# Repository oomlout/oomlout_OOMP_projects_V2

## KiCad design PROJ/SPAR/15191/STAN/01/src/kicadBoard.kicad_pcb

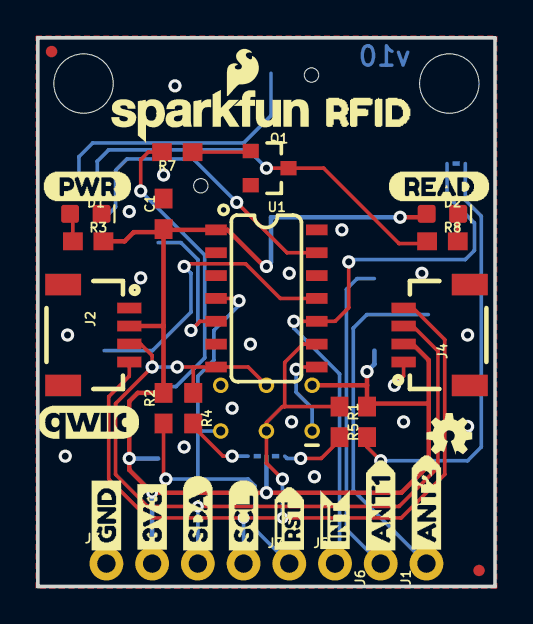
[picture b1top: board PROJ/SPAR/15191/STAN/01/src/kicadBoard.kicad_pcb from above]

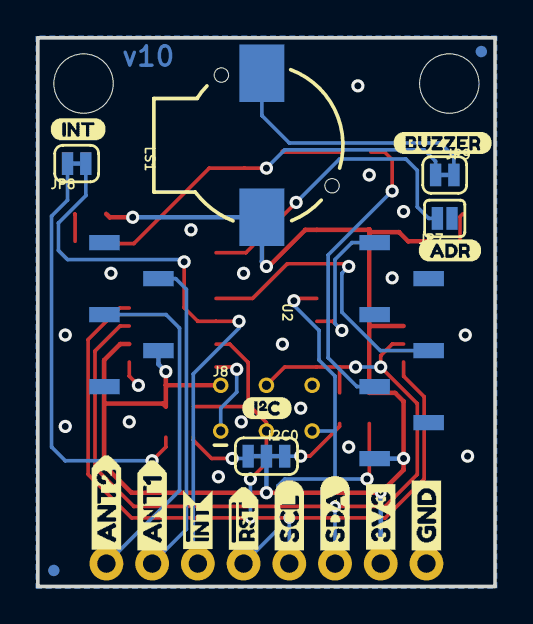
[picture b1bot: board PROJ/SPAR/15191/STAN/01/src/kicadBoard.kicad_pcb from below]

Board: 2 copper layers, 25.4 x 30.5 mm, 59 parts (21 on the bottom side), 21 nets.

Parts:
C1: 0.1uF; 0603
D1: RED; LED-0603
D2: BLUE; LED-0603
FRAME1: FRAME-LETTER; CREATIVE_COMMONS
I2C0: SMT-JUMPER_3_2-NC_TRACE_SILK
J1, J5, J6, J7: 1X01_NO_SILK
J2, J4: 1X04_1MM_RA
J3: PTH; 1X04_NO_SILK
J8: AVR_SPI_PROG_3X2TESTPOINTS; 2X3_TEST_POINTS
JP1, JP2, JP5, JP6: FIDUCIALUFIDUCIAL; MICRO-FIDUCIAL
JP3, JP4: STAND-OFF
JP7: ADR; SMT-JUMPER_2_NO_SILK
JP8: INT; SMT-JUMPER_2_NC_TRACE_SILK
JP9: BUZZ; SMT-JUMPER_2_NC_TRACE_SILK
LOGO1: OSHW-LOGOMINI; OSHW-LOGO-MINI
LOGO3: SFE_LOGO_NAME_FLAME.1_INCH; SFE_LOGO_NAME_FLAME_.1
LS1: BUZZER-SMD; BUZZER-CCV
Q1: 600mA/40V; SOT23-3
R1, R2: 10k; 0603
R3, R7, R8: 1k; 0603
R4, R5: 2.2k; 0603
U1: ATTINY84-ARDUINO; SO14
U2: ID-12/20SMD; ID-12_SMD
U$1: QWIIC_COPYRIGHT_SMALL
U$2: I_SUPER2_C-()-03
U$3, U$17: ANT20
U$4: PWR-()-04
U$5, U$26: RST#-[_
U$6, U$23: SDA-[)
U$7, U$22: SCL-[)
U$8: RFID0
U$9, U$25: GND-04
U$10, U$24: 3V3-04
U$11, U$21: INT#-[_
U$12: ADR0
U$13: INT0
U$15: BUZZER0
U$16, U$20: ANT10
U$18: READ0

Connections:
3.3V: C1.1, D2.A, I2C0.2, J2.2, J3.2, J4.2, J8.2, LS1.+, R1.2, R2.2, R3.2, U1.1, U2.2, U2.11
ANT1: J1.1, U2.3
ANT2: J6.1, U2.4
DATA_UART: U1.11, U2.9
GND: C1.2, D1.C, J2.1, J3.1, J4.1, J8.6, JP7.1, Q1.2, U1.14, U2.1, U2.7
LED_BUZZ: R7.2, U2.10
MISO: J8.1, U1.8
unnamed: I2C0.1, R5.2
unnamed: I2C0.3, R4.2
unnamed: D1.A, R3.1
unnamed: JP8.2, R1.1
unnamed: D2.C, R8.2
unnamed: JP7.2, U1.13
unnamed: Q1.1, R7.1
unnamed: JP9.1, Q1.3, R8.1
unnamed: JP9.2, LS1.-
SCL/SCK: J2.4, J3.4, J4.4, J8.3, R5.1, U1.9
SDA/MOSI: J2.3, J3.3, J4.3, J8.4, R4.1, U1.7
TAG_IN_RANGE: U1.5, U2.6
~INT: J5.1, JP8.1, U1.10
~RST: J7.1, J8.5, R2.1, U1.4

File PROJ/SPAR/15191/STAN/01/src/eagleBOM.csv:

"Part";"Value";"Device";"Package";"Description";"PROD_ID";"VALUE";
"C1";"0.1uF";"0.1UF-0603-25V-(+80/-20%)";"0603";"0.1µF ceramic capacitors";"CAP-00810";"0.1uF";
"D1";"RED";"LED-RED0603";"LED-0603";"Red SMD LED";"DIO-00819";"RED";
"D2";"BLUE";"LED-BLUE0603";"LED-0603";"Blue SMD LED";"DIO-08575";"BLUE";
"FRAME1";"FRAME-LETTER";"FRAME-LETTER";"CREATIVE_COMMONS";"Schematic Frame - Letter";"";"";
"I2C";"";"JUMPER-SMT_3_2-NC_TRACE_SILK";"SMT-JUMPER_3_2-NC_TRACE_SILK";"Normally closed trace jumper (2 of 2 connections)";"";"";
"J1";"";"CONN_01PTH_NO_SILK_YES_STOP";"1X01_NO_SILK";"Single connection point. Often used as Generic Header-pin footprint for 0.1 inch spaced/style header connections";"";"";
"J2";"";"QWIIC_CONNECTORJS-1MM";"1X04_1MM_RA";"SparkFun I2C Standard Qwiic Connector";"CONN-13694";"";
"J3";"PTH";"I2C_STANDARD_NO_SILK";"1X04_NO_SILK";"SparkFun I2C Standard Pinout Header";"";"";
"J4";"";"QWIIC_CONNECTORJS-1MM";"1X04_1MM_RA";"SparkFun I2C Standard Qwiic Connector";"CONN-13694";"";
"J5";"";"CONN_01PTH_NO_SILK_YES_STOP";"1X01_NO_SILK";"Single connection point. Often used as Generic Header-pin footprint for 0.1 inch spaced/style header connections";"";"";
"J6";"";"CONN_01PTH_NO_SILK_YES_STOP";"1X01_NO_SILK";"Single connection point. Often used as Generic Header-pin footprint for 0.1 inch spaced/style header connections";"";"";
"J7";"";"CONN_01PTH_NO_SILK_YES_STOP";"1X01_NO_SILK";"Single connection point. Often used as Generic Header-pin footprint for 0.1 inch spaced/style header connections";"";"";
"J8";"AVR_SPI_PROG_3X2TESTPOINTS";"AVR_SPI_PROG_3X2TESTPOINTS";"2X3_TEST_POINTS";"AVR ISP 6 Pin";"";"";
"JP1";"FIDUCIALUFIDUCIAL";"FIDUCIALUFIDUCIAL";"MICRO-FIDUCIAL";"Fiducial Alignment Points";"";"";
"JP2";"FIDUCIALUFIDUCIAL";"FIDUCIALUFIDUCIAL";"MICRO-FIDUCIAL";"Fiducial Alignment Points";"";"";
"JP3";"STAND-OFF";"STAND-OFF";"STAND-OFF";"Stand Off";"";"";
"JP4";"STAND-OFF";"STAND-OFF";"STAND-OFF";"Stand Off";"";"";
"JP5";"FIDUCIALUFIDUCIAL";"FIDUCIALUFIDUCIAL";"MICRO-FIDUCIAL";"Fiducial Alignment Points";"";"";
"JP6";"FIDUCIALUFIDUCIAL";"FIDUCIALUFIDUCIAL";"MICRO-FIDUCIAL";"Fiducial Alignment Points";"";"";
"JP7";"ADR";"JUMPER-SMT_2_NO_SILK";"SMT-JUMPER_2_NO_SILK";"Normally open jumper";"";"";
"JP8";"INT";"JUMPER-SMT_2_NC_TRACE_SILK";"SMT-JUMPER_2_NC_TRACE_SILK";"Normally closed trace jumper";"";"";
"JP9";"BUZZ";"JUMPER-SMT_2_NC_TRACE_SILK";"SMT-JUMPER_2_NC_TRACE_SILK";"Normally closed trace jumper";"";"";
"LOGO1";"OSHW-LOGOMINI";"OSHW-LOGOMINI";"OSHW-LOGO-MINI";"Open-Source Hardware (OSHW) Logo";"";"";
"LOGO3";"SFE_LOGO_NAME_FLAME.1_INCH";"SFE_LOGO_NAME_FLAME.1_INCH";"SFE_LOGO_NAME_FLAME_.1";"SparkFun Font Logo w/ Flame";"";"";
"LS1";"BUZZER-SMD";"BUZZER-SMD";"BUZZER-CCV";"Buzzer";"COMP-08568";"";
"Q1";"600mA/40V";"TRANS_NPN-MMBT2222AL";"SOT23-3";"NPN transistor";"TRANS-08049";"600mA/40V";
"R1";"10k";"10KOHM-0603-1/10W-1%";"0603";"10kΩ resistor";"RES-00824";"10k";
"R2";"10k";"10KOHM-0603-1/10W-1%";"0603";"10kΩ resistor";"RES-00824";"10k";
"R3";"1k";"1KOHM-0603-1/10W-1%";"0603";"1kΩ resistor";"RES-07856";"1k";
"R4";"2.2k";"2.2KOHM-0603-1/10W-1%";"0603";"2.2kΩ resistor";"RES-08272";"2.2k";
"R5";"2.2k";"2.2KOHM-0603-1/10W-1%";"0603";"2.2kΩ resistor";"RES-08272";"2.2k";
"R7";"1k";"1KOHM-0603-1/10W-1%";"0603";"1kΩ resistor";"RES-07856";"1k";
"R8";"1k";"1KOHM-0603-1/10W-1%";"0603";"1kΩ resistor";"RES-07856";"1k";
"U1";"ATTINY84-ARDUINO";"ATTINY84-ARDUINO";"SO14";"";"IC-11285";"";
"U2";"ID-12/20SMD";"ID-12/20SMD";"ID-12_SMD";"ID Innovations 125kHz RFID Reader (ID2, ID3, ID12, and ID20)";"CONN-09345, CONN-09344";"";

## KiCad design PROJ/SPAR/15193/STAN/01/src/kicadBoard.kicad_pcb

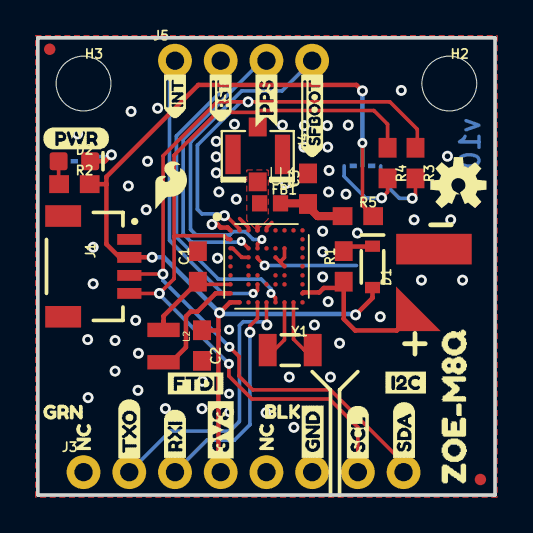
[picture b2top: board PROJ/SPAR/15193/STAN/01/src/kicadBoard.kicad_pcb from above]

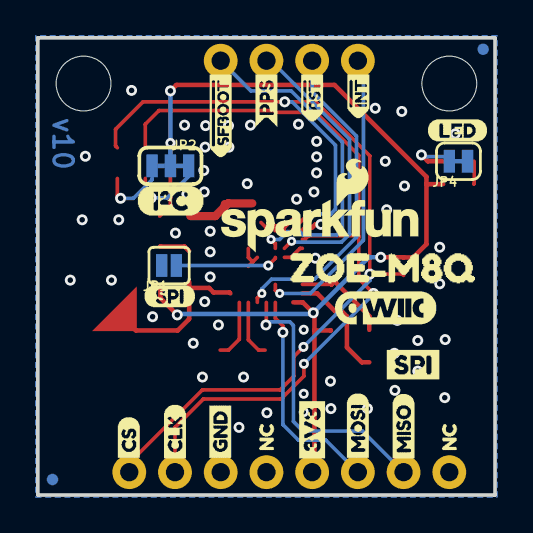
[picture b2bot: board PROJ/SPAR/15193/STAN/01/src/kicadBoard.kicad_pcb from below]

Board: 2 copper layers, 25.4 x 25.4 mm, 69 parts (24 on the bottom side), 23 nets.

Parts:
B1: ML414H_IV01E_BATTERY; ML414H_IV01E
C1: 4.7uF; 0603
C2: 0.1uF; 0603
C3: 47pF; 0603
D1: 0.5A/40V/420mV; SOD-323
D2: RED; LED-0603
FB1: FERRITE_BEAD-120_OHM-0402; 0402
FD1, FD2, FD3, FD4: FIDUCIALUFIDUCIAL; FIDUCIAL-MICRO
FRAME1: FRAME-LETTER; CREATIVE_COMMONS
H2, H3: STAND-OFFTIGHT; STAND-OFF-TIGHT
J1: JST04_1MM_RA
J3: 1X08_NO_SILK
J4: U.FL
J5: 1X04_NO_SILK
JP1: JUMPER-SMT_2_NO_SILK; SMT-JUMPER_2_NO_SILK
JP2: JUMPER-SMT_3_2-NC_TRACE_SILK; SMT-JUMPER_3_2-NC_TRACE_SILK
JP4: JUMPER-SMT_2_NC_TRACE_SILK; SMT-JUMPER_2_NC_TRACE_SILK
L2: 2.2uH; 0806
LOGO1: SFE_LOGO_NAME_FLAME.1_INCH; SFE_LOGO_NAME_FLAME_.1
LOGO2: OSHW-LOGOS; OSHW-LOGO-S
LOGO3: SFE_LOGO_FLAME.1_INCH; SFE_LOGO_FLAME_.1
LOGO4: SPECIAL_INSTRUCTIONS-ORDERING; ORDERING_INSTRUCTIONS
R1: 3.3k; 0603
R2: 1k; 0603
R3, R4: 2.2k; 0603
R5: 10; 0603
U1: U-BLOX_ZOE_M8Q-0-10; UBLOX_ZOE_M8-0-10
U$1, U$10: 3V3-03
U$2: SDA0
U$3: SCL0
U$4, U$7: GND0
U$5: CS0
U$6: MISO0
U$8: CLK0
U$9, U$17: SPI0
U$11, U$18: #INT0
U$12, U$21: #RST0
U$13, U$23: PPS0
U$14, U$24: #SFBOOT0
U$15: TXO0
U$16, U$30: ZOE#M8Q0
U$19: RXI0
U$20: BLK0
U$22, U$33, U$34, U$35: NC0
U$25: LED0
U$26: PWR-()-03
U$27: MOSI0
U$28: FTDI0
U$29: I2C0
U$31: GRN0
U$32: I_SUPER2_C-()-04
U$36: QWIIC_COPYRIGHT_SMALL
Y1: 32.768kHz; CRYSTAL-SMD-3.2X1.5MM

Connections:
3.3V: C2.1, D1.A, J1.2, J3.4, JP2.2, R2.2, R5.2, U1.24, U1.25
ANT: FB1.1, J4.FEED, U1.4
D_SEL: JP1.1, U1.48
GND: B1.-, C1.2, C2.2, C3.2, J1.1, J3.6, J4.1, J4.2, JP1.2, JP4.1, U1.1, U1.3, U1.5, U1.7, U1.8, U1.9, U1.10, U1.11, U1.12, U1.17, U1.23, U1.29, U1.31, U1.37, U1.38, U1.39, U1.40, U1.41, U1.44, U1.46, U1.47, U1.49
unnamed: JP2.1, R3.2
unnamed: D1.C, R1.2
unnamed: JP2.3, R4.2
unnamed: D2.A, R2.1
unnamed: C1.1, L2.1, U1.27
unnamed: L2.2, U1.26
unnamed: D2.C, JP4.2
unnamed: C3.1, FB1.2, R5.1
unnamed: U1.18, Y1.P$2
unnamed: U1.19, Y1.P$1
RXI/MOSI: J3.3, U1.22
SCL/CLK: J1.4, J3.7, R4.1, U1.32
SDA/CS: J1.3, J3.8, R3.1, U1.2
TIMEPULSE: J5.3, U1.33
TXO/MISO: J3.2, U1.21
V_BATT: B1.+, R1.1, U1.16
~INT: J5.1, U1.43
~RESET: J5.2, U1.20
~SAFEBOOT: J5.4, U1.34

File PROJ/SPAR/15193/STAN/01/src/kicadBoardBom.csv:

"Id";"Designator";"Package";"Quantity";"Designation";"Supplier and ref";
1;"H3,H2";"STAND-OFF-TIGHT";2;"STAND-OFFTIGHT";;;
2;"U1";"UBLOX_ZOE_M8-0-10";1;"U-BLOX_ZOE_M8Q-0-10";;;
3;"U$14,U$24";"#SFBOOT0";2;"";;;
4;"U$22,U$33,U$35,U$34";"NC0";4;"";;;
5;"L2";"0806";1;"2.2uH";;;
6;"U$29";"I2C0";1;"";;;
7;"U$28";"FTDI0";1;"";;;
8;"R4,R3";"0603";2;"2.2k";;;
9;"C1";"0603";1;"4.7uF";;;
10;"U$11,U$18";"#INT0";2;"";;;
11;"FB1";"0402";1;"FERRITE_BEAD-120_OHM-0402";;;
12;"J3";"1X08_NO_SILK";1;"";;;
13;"C3";"0603";1;"47pF";;;
14;"Y1";"CRYSTAL-SMD-3.2X1.5MM";1;"32.768kHz";;;
15;"U$3";"SCL0";1;"";;;
16;"FD4,FD1,FD2,FD3";"FIDUCIAL-MICRO";4;"FIDUCIALUFIDUCIAL";;;
17;"R1";"0603";1;"3.3k";;;
18;"U$15";"TXO0";1;"";;;
19;"J4";"U.FL";1;"U.FL";;;
20;"R5";"0603";1;"10";;;
21;"B1";"ML414H_IV01E";1;"ML414H_IV01E_BATTERY";;;
22;"U$1,U$10";"3V3-03";2;"";;;
23;"LOGO4";"ORDERING_INSTRUCTIONS";1;"SPECIAL_INSTRUCTIONS-ORDERING";;;
24;"C2";"0603";1;"0.1uF";;;
25;"U$19";"RXI0";1;"";;;
26;"D2";"LED-0603";1;"RED";;;
27;"D1";"SOD-323";1;"0.5A/40V/420mV";;;
28;"U$12,U$21";"#RST0";2;"";;;
29;"U$31";"GRN0";1;"";;;
30;"U$4,U$7";"GND0";2;"";;;
31;"J5";"1X04_NO_SILK";1;"";;;
32;"U$26";"PWR-()-03";1;"";;;
33;"J1";"JST04_1MM_RA";1;"";;;
34;"R2";"0603";1;"1k";;;
35;"U$2";"SDA0";1;"";;;
36;"LOGO3";"SFE_LOGO_FLAME_.1";1;"SFE_LOGO_FLAME.1_INCH";;;
37;"U$20";"BLK0";1;"";;;
38;"U$30,U$16";"ZOE#M8Q0";2;"";;;
39;"U$23,U$13";"PPS0";2;"";;;
40;"LOGO2";"OSHW-LOGO-S";1;"OSHW-LOGOS";;;
41;"FRAME1";"CREATIVE_COMMONS";1;"FRAME-LETTER";;;
42;"U$36";"QWIIC_COPYRIGHT_SMALL";1;"";;;
43;"LOGO1";"SFE_LOGO_NAME_FLAME_.1";1;"SFE_LOGO_NAME_FLAME.1_INCH";;;
44;"JP1";"SMT-JUMPER_2_NO_SILK";1;"JUMPER-SMT_2_NO_SILK";;;
45;"U$27";"MOSI0";1;"";;;
46;"U$8";"CLK0";1;"";;;
47;"U$9,U$17";"SPI0";2;"";;;
48;"U$5";"CS0";1;"";;;
49;"U$25";"LED0";1;"";;;
50;"JP4";"SMT-JUMPER_2_NC_TRACE_SILK";1;"JUMPER-SMT_2_NC_TRACE_SILK";;;
51;"JP2";"SMT-JUMPER_3_2-NC_TRACE_SILK";1;"JUMPER-SMT_3_2-NC_TRACE_SILK";;;
52;"U$6";"MISO0";1;"";;;
53;"U$32";"I_SUPER2_C-()-04";1;"";;;

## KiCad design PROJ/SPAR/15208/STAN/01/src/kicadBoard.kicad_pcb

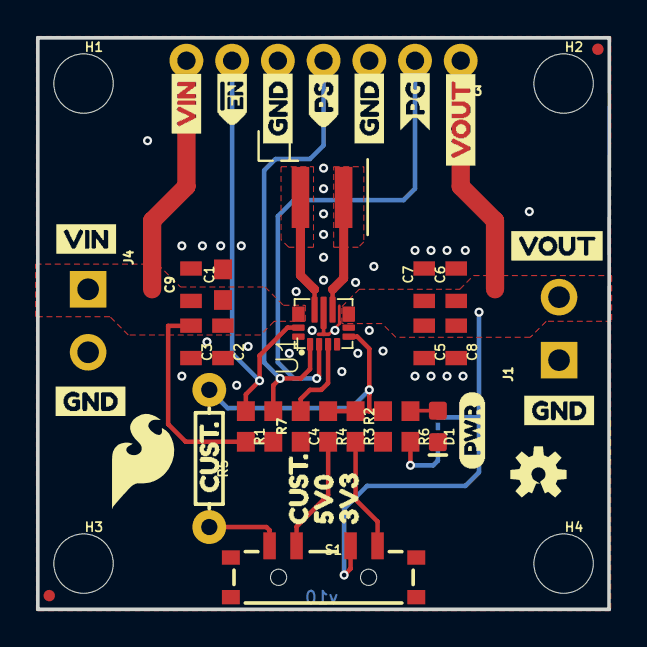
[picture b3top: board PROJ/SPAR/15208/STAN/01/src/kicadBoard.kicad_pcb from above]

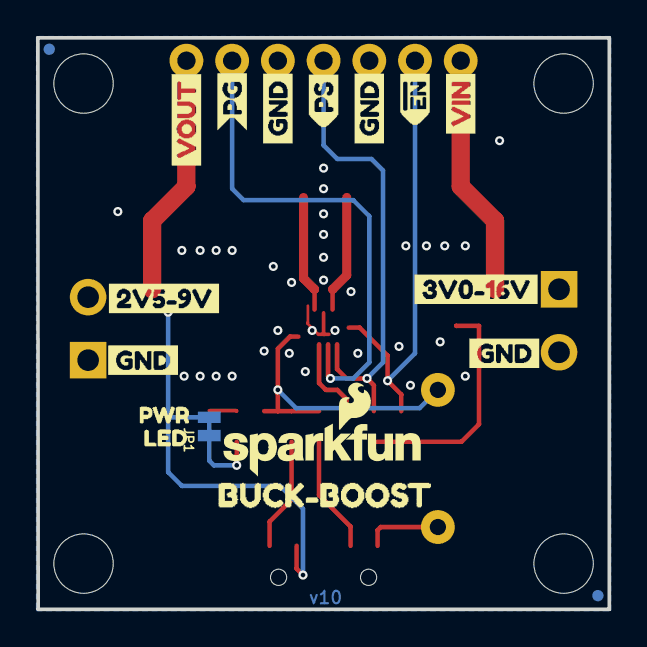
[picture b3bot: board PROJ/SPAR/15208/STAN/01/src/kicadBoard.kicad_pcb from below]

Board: 2 copper layers, 31.8 x 31.8 mm, 67 parts (18 on the bottom side), 15 nets.

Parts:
C1, C4: 0.1uF; 0603
C2, C3, C5, C9: 10uF; 0805
C6, C7, C8: 22uF; 0805
D1: RED; LED-0603
FD1, FD2, FD3, FD4: FIDUCIALUFIDUCIAL; FIDUCIAL-MICRO
FRAME1: FRAME-LETTER; CREATIVE_COMMONS
H1, H2, H3, H4: STAND-OFF
J1, J4: SCREWTERMINAL-3.5MM-2-NS
J3: 1X07_NO_SILK
JP1: SMT-JUMPER_2_NC_TRACE_NO-SILK
L1: 1.5uH; XFL4020
LOGO1: SFE_LOGO_NAME_FLAME.1_INCH; SFE_LOGO_NAME_FLAME_.1
LOGO2: OSHW-LOGOS; OSHW-LOGO-S
LOGO3: SPECIAL_INSTRUCTIONS-ORDERING; ORDERING_INSTRUCTIONS
R1, R7: 10k; 0603
R2: 68.1k; 0603
R3: 213k; 0603
R4: 365k; 0603
R5: CUSTOM; AXIAL-0.3
R6: 1k; 0603
S1: SWITCH_SP3T_SMD
U1: TPS63070; VQFN-15-HR(3X2.5)
U$1: PWR2
U$2, U$17: CUST#7
U$3, U$25: VIN0
U$4, U$20, U$30, U$31: GND1
U$5: VIN3
U$6, U$7, U$12, U$13: GND4
U$8: VOUT5
U$9: SFE_LOGO_FLAME_.2
U$10: 3V0#16V6
U$11: PWR1
U$14: 2V5#9V1
U$15: BUCK#BOOST18
U$16: LED0
U$18: 5V08
U$19: 3V39
U$21, U$26: VOUT2
U$22, U$28: #EN0
U$23, U$29: PS1
U$24, U$27: PG2

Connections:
FB: R2.2, R3.1, R4.1, R5.P$1, U1.P$5
GND: C1.2, C2.2, C3.2, C4.2, C5.2, C6.2, C7.2, C8.2, C9.2, D1.C, J1.1, J3.3, J3.5, J4.2, R2.1, U1.P$4, U1.P$6, U1.P$10, U1.P$15
unnamed: L1.P$1, U1.P$11
unnamed: L1.P$2, U1.P$9
unnamed: R5.P$2, S1.1
unnamed: R4.2, S1.2
unnamed: C4.1, U1.P$3
unnamed: R3.2, S1.4
unnamed: JP1.1, R6.2
unnamed: D1.A, R6.1
PG: J3.2, U1.P$2
PS: J3.4, R7.1, U1.P$1
VIN: C1.1, C2.1, C3.1, C9.1, J3.7, J4.1, R1.2, R7.2, U1.P$12/13
VOUT: C5.1, C6.1, C7.1, C8.1, J1.2, J3.1, JP1.2, S1.3, U1.P$7/8
~EN: J3.6, R1.1, U1.P$14

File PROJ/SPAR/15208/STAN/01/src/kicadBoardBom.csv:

"Id";"Designator";"Package";"Quantity";"Designation";"Supplier and ref";
1;"U$23,U$29";"PS1";2;"";;;
2;"U$4,U$20,U$30,U$31";"GND1";4;"";;;
3;"U$1";"PWR2";1;"";;;
4;"U$5";"VIN3";1;"";;;
5;"R3";"0603";1;"213k";;;
6;"D1";"LED-0603";1;"RED";;;
7;"U$19";"3V39";1;"";;;
8;"C6,C8,C7";"0805";3;"22uF";;;
9;"C4,C1";"0603";2;"0.1uF";;;
10;"U$7,U$6,U$12,U$13";"GND4";4;"";;;
11;"FRAME1";"CREATIVE_COMMONS";1;"FRAME-LETTER";;;
12;"C9,C5,C2,C3";"0805";4;"10uF";;;
13;"LOGO2";"OSHW-LOGO-S";1;"OSHW-LOGOS";;;
14;"U$17,U$2";"CUST#7";2;"";;;
15;"R5";"AXIAL-0.3";1;"CUSTOM";;;
16;"R2";"0603";1;"68.1k";;;
17;"FD1,FD3,FD2,FD4";"FIDUCIAL-MICRO";4;"FIDUCIALUFIDUCIAL";;;
18;"R7,R1";"0603";2;"10k";;;
19;"H4,H1,H2,H3";"STAND-OFF";4;"STAND-OFF";;;
20;"U$9";"SFE_LOGO_FLAME_.2";1;"";;;
21;"R6";"0603";1;"1k";;;
22;"U$3,U$25";"VIN0";2;"";;;
23;"U$18";"5V08";1;"";;;
24;"LOGO3";"ORDERING_INSTRUCTIONS";1;"SPECIAL_INSTRUCTIONS-ORDERING";;;
25;"U1";"VQFN-15-HR(3X2.5)";1;"TPS63070";;;
26;"R4";"0603";1;"365k";;;
27;"U$8";"VOUT5";1;"";;;
28;"U$22,U$28";"#EN0";2;"";;;
29;"S1";"SWITCH_SP3T_SMD";1;"";;;
30;"J4,J1";"SCREWTERMINAL-3.5MM-2-NS";2;"";;;
31;"L1";"XFL4020";1;"1.5uH";;;
32;"U$24,U$27";"PG2";2;"";;;
33;"J3";"1X07_NO_SILK";1;"";;;
34;"U$21,U$26";"VOUT2";2;"";;;
35;"U$14";"2V5#9V1";1;"";;;
36;"U$16";"LED0";1;"";;;
37;"U$15";"BUCK#BOOST18";1;"";;;
38;"JP1";"SMT-JUMPER_2_NC_TRACE_NO-SILK";1;"";;;
39;"U$11";"PWR1";1;"";;;
40;"LOGO1";"SFE_LOGO_NAME_FLAME_.1";1;"SFE_LOGO_NAME_FLAME.1_INCH";;;
41;"U$10";"3V0#16V6";1;"";;;

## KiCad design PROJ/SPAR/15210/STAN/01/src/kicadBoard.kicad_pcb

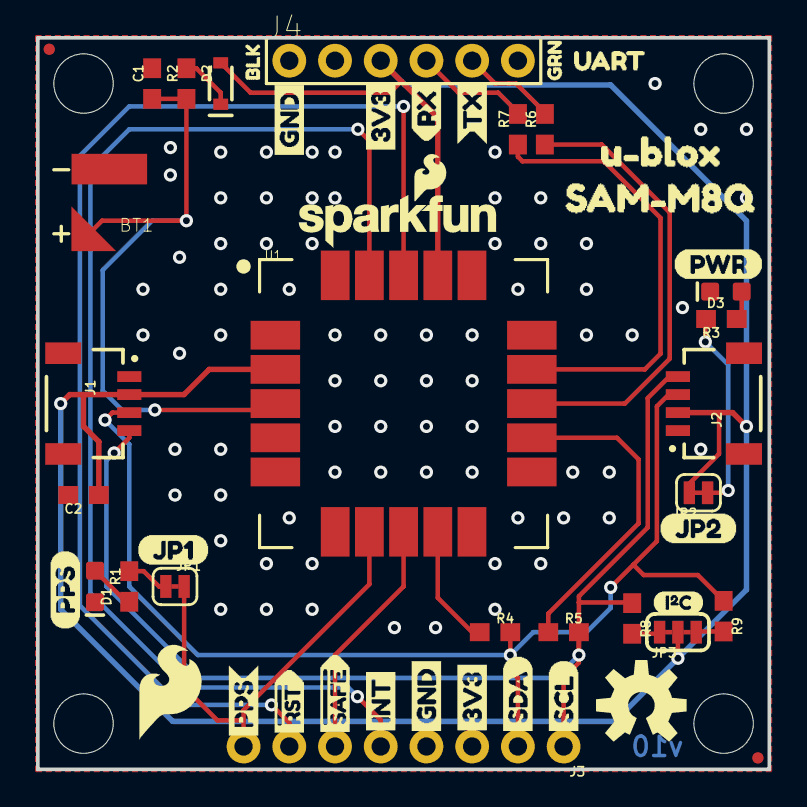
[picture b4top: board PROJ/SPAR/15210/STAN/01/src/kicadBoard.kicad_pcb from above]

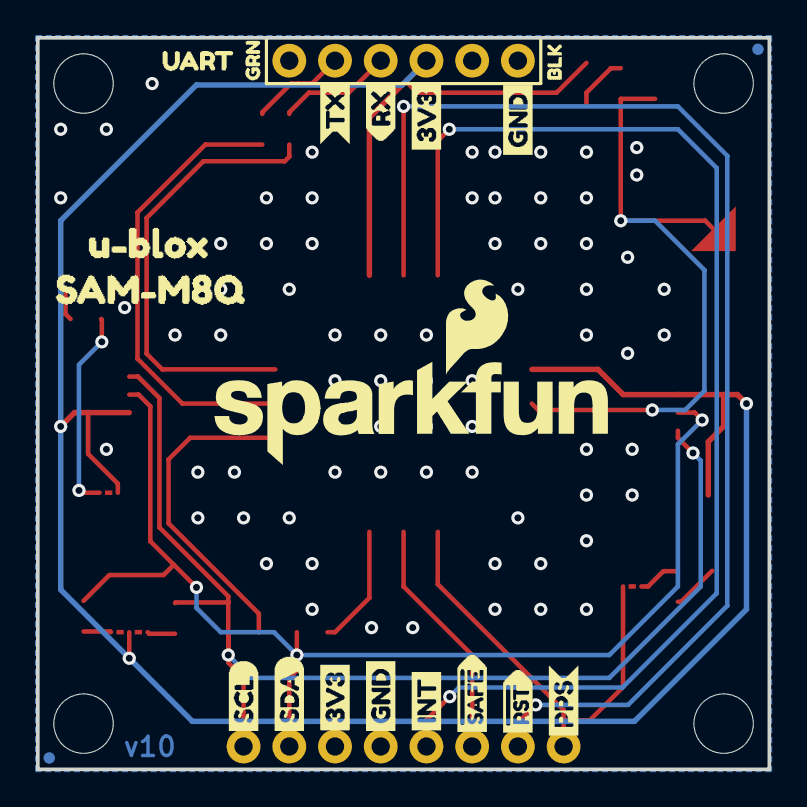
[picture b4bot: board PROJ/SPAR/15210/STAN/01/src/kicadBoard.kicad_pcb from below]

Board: 2 copper layers, 40.6 x 40.6 mm, 75 parts (20 on the bottom side), 22 nets.

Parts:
BT1: 6.8MM_COIN_CELL; ML414H_IV01E
C1, C2: 1.0uF; 0603
D1: Yellow; LED-0603
D2: 0.5A/40V/420mV; SOD-323
D3: RED; LED-0603
FD1, FD2, FD3, FD4: FIDUCIALUFIDUCIAL; FIDUCIAL-MICRO
FRAME1: FRAME-LETTER; CREATIVE_COMMONS
H1, H2, H3, H4: STAND-OFF
J1, J2: Qwiic Right Angle; JST04_1MM_RA
J3: 1X08_NO_SILK
J4: BOOT; 1X06_NO_SILK
JP1: SMT-JUMPER_2_NC_TRACE_SILK
JP2: JUMPER-SMT_2_NC_TRACE_SILK; SMT-JUMPER_2_NC_TRACE_SILK
JP3: JUMPER-SMT_3_2-NC_TRACE_SILK; SMT-JUMPER_3_2-NC_TRACE_SILK
LOGO1: SFE_LOGO_NAME_FLAME.2_INCH; SFE_LOGO_NAME_FLAME_.2
LOGO2: OSHW-LOGOM; OSHW-LOGO-M
R1, R3: 1k; 0603
R2: 3.3k; 0603
R4, R5: 22; 0603
R6, R7: 470; 0603
R8, R9: 2.2k; 0603
U1: UBLOX_SAM_M8Q-0-10; SAM-M8Q
U$1, U$4: SDA-[)
U$2: SFE_LOGO_FLAME_.2
U$3, U$5: SCL-[)
U$6, U$7, U$27, U$32: 3V3-04
U$8, U$9, U$33, U$34: GND-04
U$10: I_SUPER2_C-()-03
U$11, U$45: UART0
U$12, U$13: BLK1
U$14, U$17: GRN2
U$15, U$16: INT8
U$18: JP10
U$19, U$20: RX6
U$21, U$25: SAM#M8Q4
U$22, U$26: U#BLOX3
U$23, U$24: TX7
U$28: SFE_LOGO_NAME_FLAME_.1
U$29: PPS0
U$30: PWR0
U$31: JP20
U$35, U$36: #RST3
U$39, U$40: #SAFE1
U$43, U$44: PPS5

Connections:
3.3V: C2.1, D2.A, J1.2, J2.2, J3.3, J4.3, JP2.2, JP3.2, U1.2, U1.17
BACKUP: BT1.+, C1.1, R2.1, U1.3
GND: BT1.-, C1.2, C2.2, D1.C, D3.C, J1.1, J2.1, J3.4, J4.1, J4.2, U1.1, U1.4, U1.5, U1.6, U1.10, U1.11, U1.15, U1.16, U1.20
INT: J3.5, U1.19
unnamed: JP2.1, R3.2
unnamed: D1.A, R1.1
unnamed: D3.A, R3.1
unnamed: JP1.1, R1.2
unnamed: JP3.1, R9.2
unnamed: D2.C, R2.2
unnamed: JP3.3, R8.2
PPS: J3.8, JP1.2, U1.7
RXI: J4.4, R7.2
RXLV: R7.1, U1.14
SCL: J1.4, J2.4, J3.1, R5.2, R8.1
SCL_LV: R5.1, U1.12
SDA: J1.3, J2.3, J3.2, R4.2, R9.1
SDA_LV: R4.1, U1.9
TXLV: R6.1, U1.13
TXO: J4.5, R6.2
~RESET: J3.7, U1.18
~SAFE: J3.6, U1.8

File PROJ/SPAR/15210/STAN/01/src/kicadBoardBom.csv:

"Id";"Designator";"Package";"Quantity";"Designation";"Supplier and ref";
1;"U$33,U$8,U$9,U$34";"GND-04";4;"";;;
2;"J4";"1X06_NO_SILK";1;"BOOT";;;
3;"U$10";"I_SUPER2_C-()-03";1;"";;;
4;"U$2";"SFE_LOGO_FLAME_.2";1;"";;;
5;"R2";"0603";1;"3.3k";;;
6;"FRAME1";"CREATIVE_COMMONS";1;"FRAME-LETTER";;;
7;"U$30";"PWR0";1;"";;;
8;"U$14,U$17";"GRN2";2;"";;;
9;"FD1,FD3,FD2,FD4";"FIDUCIAL-MICRO";4;"FIDUCIALUFIDUCIAL";;;
10;"U$21,U$25";"SAM#M8Q4";2;"";;;
11;"U$29";"PPS0";1;"";;;
12;"U$19,U$20";"RX6";2;"";;;
13;"U$43,U$44";"PPS5";2;"";;;
14;"U$6,U$27,U$7,U$32";"3V3-04";4;"";;;
15;"U$23,U$24";"TX7";2;"";;;
16;"U1";"SAM-M8Q";1;"UBLOX_SAM_M8Q-0-10";;;
17;"U$45,U$11";"UART0";2;"";;;
18;"U$1,U$4";"SDA-[)";2;"";;;
19;"D2";"SOD-323";1;"0.5A/40V/420mV";;;
20;"JP1";"SMT-JUMPER_2_NC_TRACE_SILK";1;"";;;
21;"BT1";"ML414H_IV01E";1;"6.8MM_COIN_CELL";;;
22;"U$28";"SFE_LOGO_NAME_FLAME_.1";1;"";;;
23;"R7,R6";"0603";2;"470";;;
24;"U$35,U$36";"#RST3";2;"";;;
25;"J3";"1X08_NO_SILK";1;"";;;
26;"R9,R8";"0603";2;"2.2k";;;
27;"JP2";"SMT-JUMPER_2_NC_TRACE_SILK";1;"JUMPER-SMT_2_NC_TRACE_SILK";;;
28;"R4,R5";"0603";2;"22";;;
29;"JP3";"SMT-JUMPER_3_2-NC_TRACE_SILK";1;"JUMPER-SMT_3_2-NC_TRACE_SILK";;;
30;"U$12,U$13";"BLK1";2;"";;;
31;"D1";"LED-0603";1;"Yellow";;;
32;"H1,H3,H4,H2";"STAND-OFF";4;"STAND-OFF";;;
33;"U$39,U$40";"#SAFE1";2;"";;;
34;"U$18";"JP10";1;"";;;
35;"C1,C2";"0603";2;"1.0uF";;;
36;"LOGO2";"OSHW-LOGO-M";1;"OSHW-LOGOM";;;
37;"R3,R1";"0603";2;"1k";;;
38;"U$31";"JP20";1;"";;;
39;"J2,J1";"JST04_1MM_RA";2;"Qwiic Right Angle";;;
40;"U$3,U$5";"SCL-[)";2;"";;;
41;"U$15,U$16";"INT8";2;"";;;
42;"D3";"LED-0603";1;"RED";;;
43;"U$26,U$22";"U#BLOX3";2;"";;;
44;"LOGO1";"SFE_LOGO_NAME_FLAME_.2";1;"SFE_LOGO_NAME_FLAME.2_INCH";;;

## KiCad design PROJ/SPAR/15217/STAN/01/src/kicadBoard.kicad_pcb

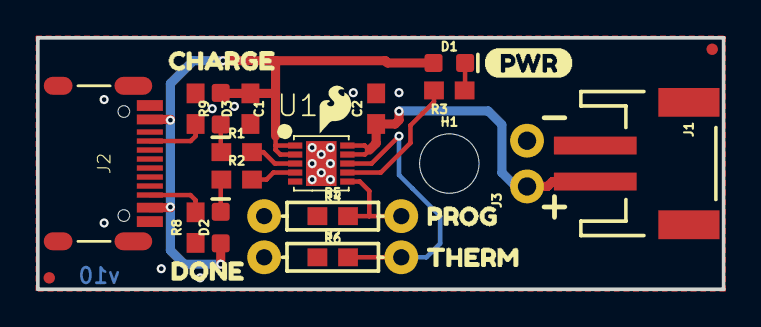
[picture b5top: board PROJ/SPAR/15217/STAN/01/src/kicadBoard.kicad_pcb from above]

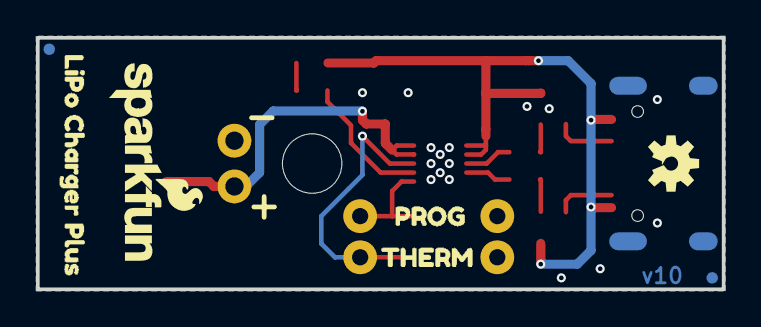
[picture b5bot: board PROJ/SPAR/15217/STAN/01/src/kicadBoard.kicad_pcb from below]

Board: 4 copper layers, 38.1 x 14.0 mm, 35 parts (7 on the bottom side), 13 nets.

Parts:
C1, C2: 10uF; 0603
D1: RED; LED-0603
D2: GREEN; LED-0603
D3: Yellow; LED-0603
FD1, FD2, FD3, FD4: FIDUCIALUFIDUCIAL; FIDUCIAL-MICRO
FRAME1: FRAME-LETTER; CREATIVE_COMMONS
H1: STAND-OFF
J1: JST-2-SMD
J2: USB-C-16P
J3: 1X02_NO_SILK
LOGO1: SFE_LOGO_NAME_FLAME.1_INCH; SFE_LOGO_NAME_FLAME_.1
LOGO2: OSHW-LOGOS; OSHW-LOGO-S
R1, R2, R3: 1.5k; 0603
R4: 1k; 0603
R5: PROG; AXIAL-0.3
R6: 10k; 0603
R7: THERM; AXIAL-0.3
R8, R9: 5.1k; 0603
U1: MCP73833; DFN-10
U$1: SFE_LOGO_FLAME_.1
U$2, U$5: PROG7
U$3: CHARGE3
U$4: DONE4
U$6, U$8: THERM8
U$7: PWR6
U$9: LIPO_CHARGER_PLUS0

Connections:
GND: C1.2, C2.2, J1.1, J2.GND, J2.GND2, J2.SHLD1, J2.SHLD2, J2.SHLD3, J2.SHLD4, J2.SHLD5, J2.SHLD6, J2.SHLD7, J2.SHLD8, J3.2, R4.1, R5.P$1, R6.1, R7.P$1, R8.1, R9.1, U1.P$5, U1.P$11
unnamed: D1.C, R3.1
unnamed: D2.C, R2.1
unnamed: D3.C, R1.1
unnamed: J2.B5, R8.2
unnamed: J2.A5, R9.2
PG: R3.2, U1.P$7
PROG: R4.2, R5.P$2, U1.P$6
STAT1: R1.2, U1.P$3
STAT2: R2.2, U1.P$4
THERM: R6.2, R7.P$2, U1.P$8
VDD: C1.1, D1.A, D2.A, D3.A, J2.VBUS1, J2.VBUS2, U1.P$1, U1.P$2
V_BATT: C2.1, J1.2, J3.1, U1.P$9, U1.P$10

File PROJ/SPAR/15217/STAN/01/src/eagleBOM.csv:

"Part";"Value";"Device";"Package";"Description";"DESIGNER";"PROD_ID";"REV";"SF_ID";"VALUE";
"C1";"10uF";"10UF-0603-6.3V-20%";"0603";"10.0µF ceramic capacitors";"";"CAP-11015";"";"";"10uF";
"C2";"10uF";"10UF-0603-6.3V-20%";"0603";"10.0µF ceramic capacitors";"";"CAP-11015";"";"";"10uF";
"D1";"RED";"LED-RED0603";"LED-0603";"Red SMD LED";"";"DIO-00819";"";"";"RED";
"D2";"GREEN";"LED-GREEN0603";"LED-0603";"Green SMD LED";"";"DIO-00821";"";"";"GREEN";
"D3";"Yellow";"LED-YELLOW0603";"LED-0603";"Yellow SMD LED";"";"DIO-09003";"";"";"Yellow";
"FD1";"FIDUCIALUFIDUCIAL";"FIDUCIALUFIDUCIAL";"FIDUCIAL-MICRO";"Fiducial Alignment Points";"";"";"";"";"";
"FD2";"FIDUCIALUFIDUCIAL";"FIDUCIALUFIDUCIAL";"FIDUCIAL-MICRO";"Fiducial Alignment Points";"";"";"";"";"";
"FD3";"FIDUCIALUFIDUCIAL";"FIDUCIALUFIDUCIAL";"FIDUCIAL-MICRO";"Fiducial Alignment Points";"";"";"";"";"";
"FD4";"FIDUCIALUFIDUCIAL";"FIDUCIALUFIDUCIAL";"FIDUCIAL-MICRO";"Fiducial Alignment Points";"";"";"";"";"";
"FRAME1";"FRAME-LETTER";"FRAME-LETTER";"CREATIVE_COMMONS";"Schematic Frame - Letter";"";"";"";"";"";
"H1";"STAND-OFF";"STAND-OFF";"STAND-OFF";"Stand Off";"";"";"";"";"";
"J1";"";"JST_2MM_MALE";"JST-2-SMD";"JST 2MM MALE RA CONNECTOR";"";"CONN-11443";"";"PRT-08612";"";
"J2";"";"USB_C16PIN";"USB-C-16P";"USB Type C 16Pin Connector";"";"CONN-14122";"";"";"";
"J3";"";"CONN_021X02_NO_SILK";"1X02_NO_SILK";"Multi connection point. Often used as Generic Header-pin footprint for 0.1 inch spaced/style header connections";"";"";"";"";"";
"LOGO1";"SFE_LOGO_NAME_FLAME.1_INCH";"SFE_LOGO_NAME_FLAME.1_INCH";"SFE_LOGO_NAME_FLAME_.1";"SparkFun Font Logo w/ Flame";"";"";"";"";"";
"LOGO2";"OSHW-LOGOS";"OSHW-LOGOS";"OSHW-LOGO-S";"Open-Source Hardware (OSHW) Logo";"";"";"";"";"";
"R1";"1.5k";"1.5KOHM-0603-1/10W-1%";"0603";"1.5kΩ resistor";"";"RES-08306";"";"";"1.5k";
"R2";"1.5k";"1.5KOHM-0603-1/10W-1%";"0603";"1.5kΩ resistor";"";"RES-08306";"";"";"1.5k";
"R3";"1.5k";"1.5KOHM-0603-1/10W-1%";"0603";"1.5kΩ resistor";"";"RES-08306";"";"";"1.5k";
"R4";"1k";"1KOHM-0603-1/10W-1%";"0603";"1kΩ resistor";"";"RES-07856";"";"";"1k";
"R5";"PROG";"RESISTORAXIAL-0.3";"AXIAL-0.3";"Generic Resistor Package";"";" ";"";"";" ";
"R6";"10k";"10KOHM-0603-1/10W-1%";"0603";"10kΩ resistor";"";"RES-00824";"";"";"10k";
"R7";"THERM";"RESISTORAXIAL-0.3";"AXIAL-0.3";"Generic Resistor Package";"";" ";"";"";" ";
"R8";"5.1k";"5.1KOHM5.1KOHM-0603-1/10W-1%";"0603";"";"";"RES-12083";"";"";"5.1k";
"R9";"5.1k";"5.1KOHM5.1KOHM-0603-1/10W-1%";"0603";"";"";"RES-12083";"";"";"5.1k";
"U1";"MCP73833";"MCP73833";"DFN-10";"";"";"IC-14369";"";"";"MCP73833";

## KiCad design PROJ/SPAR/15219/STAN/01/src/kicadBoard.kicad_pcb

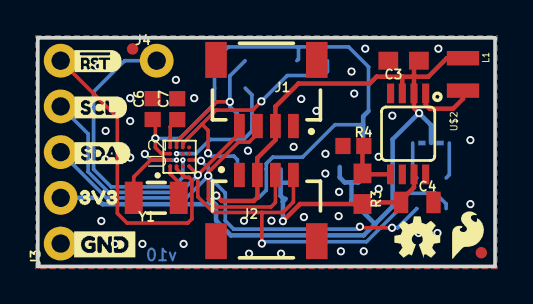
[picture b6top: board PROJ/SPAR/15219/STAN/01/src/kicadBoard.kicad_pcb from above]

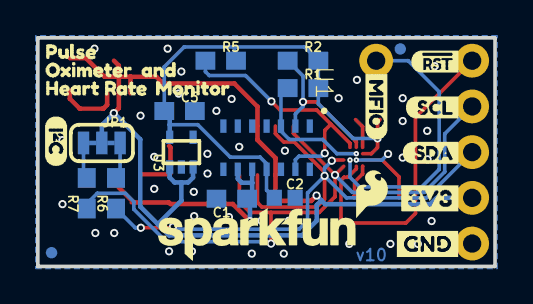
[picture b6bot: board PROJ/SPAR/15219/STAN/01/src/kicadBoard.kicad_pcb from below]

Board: 2 copper layers, 25.4 x 12.7 mm, 53 parts (28 on the bottom side), 18 nets.

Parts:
C1, C3: 10uF; 0603
C2: 0.1uF; 0402
C4: 22uF; 0805
C5: 1.0uF; 0603
C6, C7: 1.0uF; 0402
FD1, FD2, FD3, FD4: FIDUCIALUFIDUCIAL; FIDUCIAL-MICRO
FRAME1: FRAME-LETTER; CREATIVE_COMMONS
J1, J2: JST04_1MM_RA
J3: 1X05_NO_SILK
J4: 1X01_NO_SILK
JP1: JUMPER-SMT_3_2-NC_TRACE_SILK; SMT-JUMPER_3_2-NC_TRACE_SILK
L1: 2.2μH; 0806
LOGO1: SFE_LOGO_FLAME.1_INCH; SFE_LOGO_FLAME_.1
LOGO2: OSHW-LOGOMINI; OSHW-LOGO-MINI
LOGO3: SFE_LOGO_NAME.1_INCH; SFE_LOGO_NAME_.1
LOGO4: SPECIAL_INSTRUCTIONS-ORDERING; ORDERING_INSTRUCTIONS
R1, R2, R5, R6, R7: 4.7k; 0603
R3: 750K; 0603
R4: 100K; 0402
U1: MAX30101EFD; 14_PIN_OESIP
U2: MAX32664GWEA; 16_PIN_WLP
U3: 1.8V/100mA; SC70
U$1: I_SUPER2_C-()-03
U$2: PAM2401; MSOP8
U$3, U$5, U$11: GND-03
U$4, U$9: SCL0
U$6, U$8: #RST0
U$7: MFIO0
U$10, U$20: SDA0
U$12: 3V3-03
U$13: 3V3-TEXT
U$14: OXIMETER0
U$15: HEART_RATE0
U$16: MONITOR0
U$17: PULSE0
U$18: AND0
U$19: SFE_LOGO_FLAME_.1
Y1: 32.768kHz; CRYSTAL-SMD-3.2X1.5MM

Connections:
1.8V: C2.1, C5.1, C6.1, R1.2, R2.2, R5.2, U1.P11, U2.3, U3.5
3.3V: C3.1, J1.2, J2.2, J3.2, JP1.2, L1.1, U3.1, U3.3, U$2.2, U$2.3
5V: C1.1, C4.1, R3.2, U1.P9, U1.P10, U$2.7
GND: C1.2, C2.2, C3.2, C4.2, C5.2, C6.2, C7.2, J1.1, J2.1, J3.1, R4.1, U1.P4, U1.P12, U2.13, U3.2, U$2.4, U$2.8
HOST_SCL: J1.4, J2.4, J3.4, R7.1, U2.10
HOST_SDA: J1.3, J2.3, J3.3, R6.1, U2.9
unnamed: C7.1, U2.4
unnamed: R3.1, R4.2, U$2.5
unnamed: L1.2, U$2.1
unnamed: JP1.3, R6.2
unnamed: JP1.1, R7.2
unnamed: U2.1, Y1.P$1
unnamed: U2.2, Y1.P$2
SNSR_SCL: R2.1, U1.P2, U2.5
SNSR_SDA: R1.1, U1.P3, U2.14
~HR_INT: R5.1, U1.P13, U2.6
~MFIO: J4.1, U2.16
~RST: J3.5, U2.12

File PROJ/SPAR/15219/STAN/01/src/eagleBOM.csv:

"Part";"Value";"Device";"Package";"Description";"DESIGNER";"PROD_ID";"REV";"VALUE";
"C1";"10uF";"10UF-0603-6.3V-20%";"0603";"10.0µF ceramic capacitors";"";"CAP-11015";"";"10uF";
"C2";"0.1uF";"0.1UF-0402-16V-10%";"0402";"0.1µF ceramic capacitors";"";"CAP-12416";"";"0.1uF";
"C3";"10uF";"10UF-0603-6.3V-20%";"0603";"10.0µF ceramic capacitors";"";"CAP-11015";"";"10uF";
"C4";"22uF";"22UF-0805-6.3V-20%";"0805";"22µF ceramic capacitors";"";"CAP-08402";"";"22uF";
"C5";"1.0uF";"1.0UF-0603-16V-10%";"0603";"1µF ceramic capacitors";"";"CAP-00868";"";"1.0uF";
"C6";"1.0uF";"1.0UF-0402-16V-10%";"0402";"1µF ceramic capacitors";"";"CAP-12417";"";"1.0uF";
"C7";"1.0uF";"1.0UF-0402-16V-10%";"0402";"1µF ceramic capacitors";"";"CAP-12417";"";"1.0uF";
"FD1";"FIDUCIALUFIDUCIAL";"FIDUCIALUFIDUCIAL";"FIDUCIAL-MICRO";"Fiducial Alignment Points";"";"";"";"";
"FD2";"FIDUCIALUFIDUCIAL";"FIDUCIALUFIDUCIAL";"FIDUCIAL-MICRO";"Fiducial Alignment Points";"";"";"";"";
"FD3";"FIDUCIALUFIDUCIAL";"FIDUCIALUFIDUCIAL";"FIDUCIAL-MICRO";"Fiducial Alignment Points";"";"";"";"";
"FD4";"FIDUCIALUFIDUCIAL";"FIDUCIALUFIDUCIAL";"FIDUCIAL-MICRO";"Fiducial Alignment Points";"";"";"";"";
"FRAME1";"FRAME-LETTER";"FRAME-LETTER";"CREATIVE_COMMONS";"Schematic Frame - Letter";"";"";"";"";
"J1";"";"QWIIC_CONNECTORJS-1MM";"JST04_1MM_RA";"SparkFun I2C Standard Qwiic Connector";"";"CONN-13694";"";"";
"J2";"";"QWIIC_CONNECTORJS-1MM";"JST04_1MM_RA";"SparkFun I2C Standard Qwiic Connector";"";"CONN-13694";"";"";
"J3";"";"CONN_05NO_SILK";"1X05_NO_SILK";"Multi connection point. Often used as Generic Header-pin footprint for 0.1 inch spaced/style header connections";"";"";"";"";
"J4";"";"CONN_01PTH_NO_SILK_YES_STOP";"1X01_NO_SILK";"Single connection point. Often used as Generic Header-pin footprint for 0.1 inch spaced/style header connections";"";"";"";"";
"JP1";"JUMPER-SMT_3_2-NC_TRACE_SILK";"JUMPER-SMT_3_2-NC_TRACE_SILK";"SMT-JUMPER_3_2-NC_TRACE_SILK";"Normally closed trace jumper (2 of 2 connections)";"";"";"";"";
"L1";"2.2μH";"2.2μH_SHIELDED_INDUCTOR";"0806";"Murata 2.2uH Inductor";"";"NDUC-14257";"";"";
"LOGO1";"SFE_LOGO_FLAME.1_INCH";"SFE_LOGO_FLAME.1_INCH";"SFE_LOGO_FLAME_.1";"SparkFun Flame Logo";"";"";"";"";
"LOGO2";"OSHW-LOGOMINI";"OSHW-LOGOMINI";"OSHW-LOGO-MINI";"Open-Source Hardware (OSHW) Logo";"";"";"";"";
"LOGO3";"SFE_LOGO_NAME.1_INCH";"SFE_LOGO_NAME.1_INCH";"SFE_LOGO_NAME_.1";"SparkFun Font Logo";"";"";"";"";
"LOGO4";"SPECIAL_INSTRUCTIONS-ORDERING";"SPECIAL_INSTRUCTIONS-ORDERING";"ORDERING_INSTRUCTIONS";"Special Ordering/Production Instructions Alert";"";"";"";"";
"R1";"4.7k";"4.7KOHM-0603-1/10W-1%";"0603";"4.7kΩ resistor";"";"RES-07857";"";"4.7k";
"R2";"4.7k";"4.7KOHM-0603-1/10W-1%";"0603";"4.7kΩ resistor";"";"RES-07857";"";"4.7k";
"R3";"750K";"750KOHM-0603-1/10W-1%";"0603";"750Ω resistor";"";"RES-13768";"";"750K";
"R4";"100K";"100KOHM-0402-1/16W-1%";"0402";"100kΩ resistor";"";"RES-13495";"";"100K";
"R5";"4.7k";"4.7KOHM-0603-1/10W-1%";"0603";"4.7kΩ resistor";"";"RES-07857";"";"4.7k";
"R6";"4.7k";"4.7KOHM-0603-1/10W-1%";"0603";"4.7kΩ resistor";"";"RES-07857";"";"4.7k";
"R7";"4.7k";"4.7KOHM-0603-1/10W-1%";"0603";"4.7kΩ resistor";"";"RES-07857";"";"4.7k";
"U$2";"PAM2401";"PAM2401";"MSOP8";"PAM2401 - Boost PMIC";"";"IC-13769";"";"PAM2401";
"U1";"MAX30101EFD";"MAX30101EFD";"14_PIN_OESIP";"MAX30101 High-Sensitivity Pulse Oximeter and";"";"IC-14270";"";"";
"U2";"MAX32664GWEA";"MAX32664GWEA";"16_PIN_WLP";"Maxim MAX32664 Biometric Sensor Hub";"";"IC-14271";"";"";
"U3";"1.8V/100mA";"V_REG_SP6214-1.8V";"SC70";"Voltage Regulator - SP6214";"";"VREG-08428";"";"1.8V/100mA";
"Y1";"32.768kHz";"CRYSTAL-32.768KHZSMD-3.2X1.5";"CRYSTAL-SMD-3.2X1.5MM";"32.768kHz Crystal";"";"XTAL-13062";"";"32.768kHz";

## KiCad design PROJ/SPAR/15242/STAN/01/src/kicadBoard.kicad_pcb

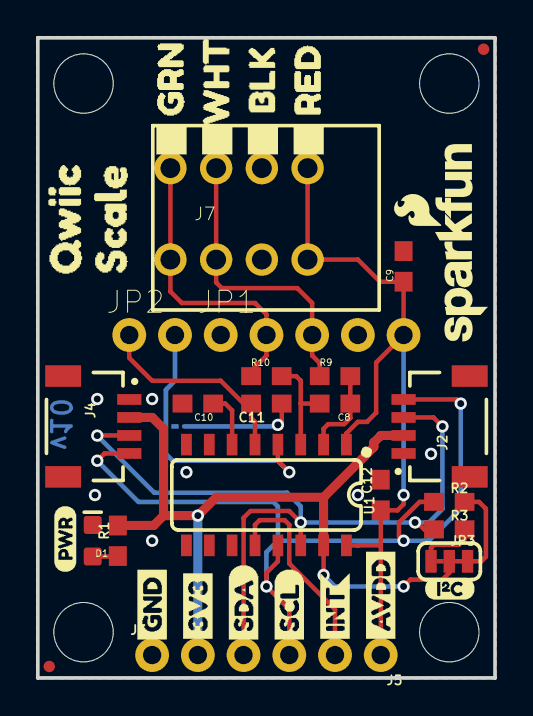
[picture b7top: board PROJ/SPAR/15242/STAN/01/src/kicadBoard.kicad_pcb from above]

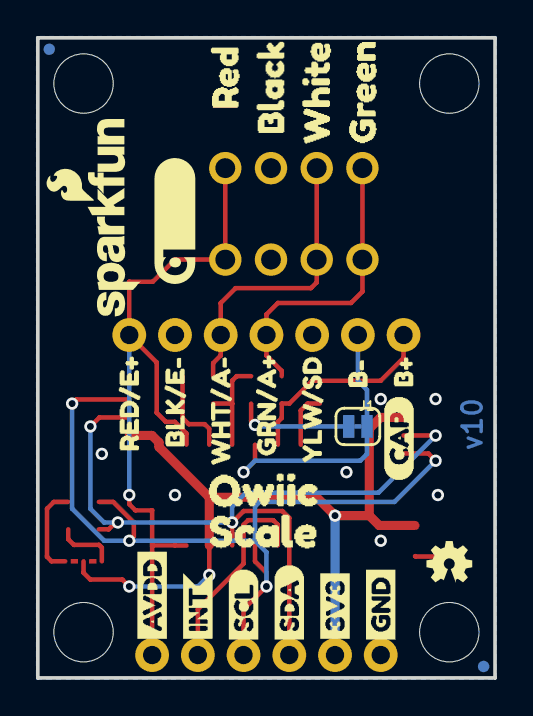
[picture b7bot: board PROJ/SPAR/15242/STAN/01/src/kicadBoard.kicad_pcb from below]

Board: 2 copper layers, 25.4 x 35.6 mm, 68 parts (26 on the bottom side), 17 nets.

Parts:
C8, C9, C10: 0.1uF; 0603
C11: 330pF; 0603
C12: 1.0uF; 0603
D1: RED; LED-0603
FRAME1: FRAME-LETTER; CREATIVE_COMMONS
J1: CAP; SMT-JUMPER_2_NC_TRACE_SILK
J2, J4: Qwiic Right Angle; JST04_1MM_RA
J3: PTH; 1X04_NO_SILK
J5: 1X02_NO_SILK
J7: Spring Terminal; 1X04_SPRING_TERMINAL
JP1: 1X05_NO_SILK
JP2: 1X02_NO_SILK
JP3: I2C; SMT-JUMPER_3_2-NC_TRACE_SILK
JP21, JP61, JP71, JP81: FIDUCIALUFIDUCIAL; MICRO-FIDUCIAL
JP31, JP41, JP91, JP101: STAND-OFF
LOGO1: OSHW-LOGOMINI; OSHW-LOGO-MINI
LOGO2, LOGO3: SFE_LOGO_NAME_FLAME.1_INCH; SFE_LOGO_NAME_FLAME_.1
R1: 1k; 0603
R2, R3: 2.2k; 0603
R9, R10: 47; 0603
U1: NAU7802; SO16
U$1, U$4: SDA-[)
U$3, U$5: SCL-[)
U$6, U$7: 3V3-04
U$8, U$9: GND-04
U$11: YLW#SD4
U$12: B#11
U$13: B#12
U$14, U$22: QWIIC2
U$15, U$21: INT0
U$16: QWIIC_LOGO_7MM; QWIIC_7MM
U$17, U$24: SCALE3
U$18: PWR-()-03
U$19: I_SUPER2_C-()-03
U$20: CAP0
U$34: BLK#E#1
U$35: GRN#A#4
U$36, U$45: AVDD4
U$37: BLACK5
U$38: BLK1
U$39: GREEN7
U$40: GRN3
U$41: RED0
U$42: RED4
U$43: WHITE6
U$44: WHT2
U$46: RED#E#2
U$48: WHT#A#3

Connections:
3.3V: J2.2, J3.2, J4.2, JP3.2, R1.2, U1.15
A+: J7.4, J7.8, JP1.2, R10.1
A-: J7.3, J7.7, JP1.3, R9.1
B+: C11.2, JP2.1, U1.5
B-: J1.2, JP2.2, U1.4
GND: C9.2, C10.2, C12.2, D1.C, J2.1, J3.1, J4.1, J7.2, J7.6, JP1.1, JP1.4, U1.7, U1.8, U1.9
INT: J5.2, U1.12
unnamed: C11.1, J1.1
unnamed: JP3.1, R3.2
unnamed: JP3.3, R2.2
unnamed: D1.A, R1.1
unnamed: C10.1, U1.6
unnamed: C8.2, R10.2, U1.3
unnamed: C8.1, R9.2, U1.2
SCL: J2.4, J3.4, J4.4, R2.1, U1.13
SDA: J2.3, J3.3, J4.3, R3.1, U1.14
VDDA: C9.1, C12.1, J5.1, J7.1, J7.5, JP1.5, U1.1, U1.16

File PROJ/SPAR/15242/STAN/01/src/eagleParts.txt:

Partlist

Exported from boardEagle.brd at 20/08/2022 03:09

EAGLE Version 9.6.2 Copyright (c) 1988-2020 Autodesk, Inc.

Assembly variant: 

Part     Value             Package                      Library                Position (inch)       Orientation

C8       0.1uF             0603                         SparkFun-Capacitors    (0.65 0.6)            R180
C9       0.1uF             0603                         SparkFun-Capacitors    (0.8 0.9)             R90
C10      0.1uF             0603                         SparkFun-Capacitors    (0.35 0.6)            R180
C11      330pF             0603                         SparkFun-Capacitors    (0.5 0.6)             R180
C12      1.0uF             0603                         SparkFun-Capacitors    (0.75 0.4)            R90
D1       RED               LED-0603                     SparkFun-LED           (0.12 0.3)            R90
J1       CAP               SMT-JUMPER_2_NC_TRACE_SILK   SparkFun-Jumpers       (0.3 0.55)            MR0
J2       Qwiic             JST04_1MM_RA                 SparkFun-Connectors    (0.8 0.55)            R90
J3       PTH               1X04_NO_SILK                 SparkFun-Connectors    (0.25 0.05)           R0
J4       Qwiic             JST04_1MM_RA                 SparkFun-Connectors    (0.2 0.55)            R270
J5                         1X02_NO_SILK                 SparkFun-Connectors    (0.75 0.05)           R180
J7       Spring Terminal   1X04_SPRING_TERMINAL         SparkFun-Connectors    (0.29 1.015)          R0
JP1                        1X05_NO_SILK                 SparkFun-Connectors    (0.4 0.75)            R0
JP2                        1X02_NO_SILK                 SparkFun-Connectors    (0.2 0.75)            R0
JP3      I2C               SMT-JUMPER_3_2-NC_TRACE_SILK SparkFun-Jumpers       (0.9 0.255)           R0
JP21     FIDUCIALUFIDUCIAL MICRO-FIDUCIAL               SparkFun               (0.975 1.375)         R90
JP61     FIDUCIALUFIDUCIAL MICRO-FIDUCIAL               SparkFun               (0.025 0.025)         R90
JP71     FIDUCIALUFIDUCIAL MICRO-FIDUCIAL               SparkFun               (0.975 1.375)         MR270
JP81     FIDUCIALUFIDUCIAL MICRO-FIDUCIAL               SparkFun               (0.025 0.025)         MR270
R1       1k                0603                         SparkFun-Resistors     (0.175 0.3)           R90
R2       2.2k              0603                         SparkFun-Resistors     (0.9 0.385)           R0
R3       2.2k              0603                         SparkFun-Resistors     (0.9 0.325)           R0
R9       47                0603                         SparkFun-Resistors     (0.65 0.66)           R0
R10      47                0603                         SparkFun-Resistors     (0.5 0.66)            R0
U1       NAU7802           SO16                         SparkFun-IC-Conversion (0.5 0.4)             R180

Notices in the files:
parts and their libraries:
RELEASED UNDER THE CREATIVE COMMONS ATTRIBUTION SHARE-ALIKE 4.0 LICENSE
HTTPS://CREATIVECOMMONS.ORG/LICENSES/BY-SA/4.0
